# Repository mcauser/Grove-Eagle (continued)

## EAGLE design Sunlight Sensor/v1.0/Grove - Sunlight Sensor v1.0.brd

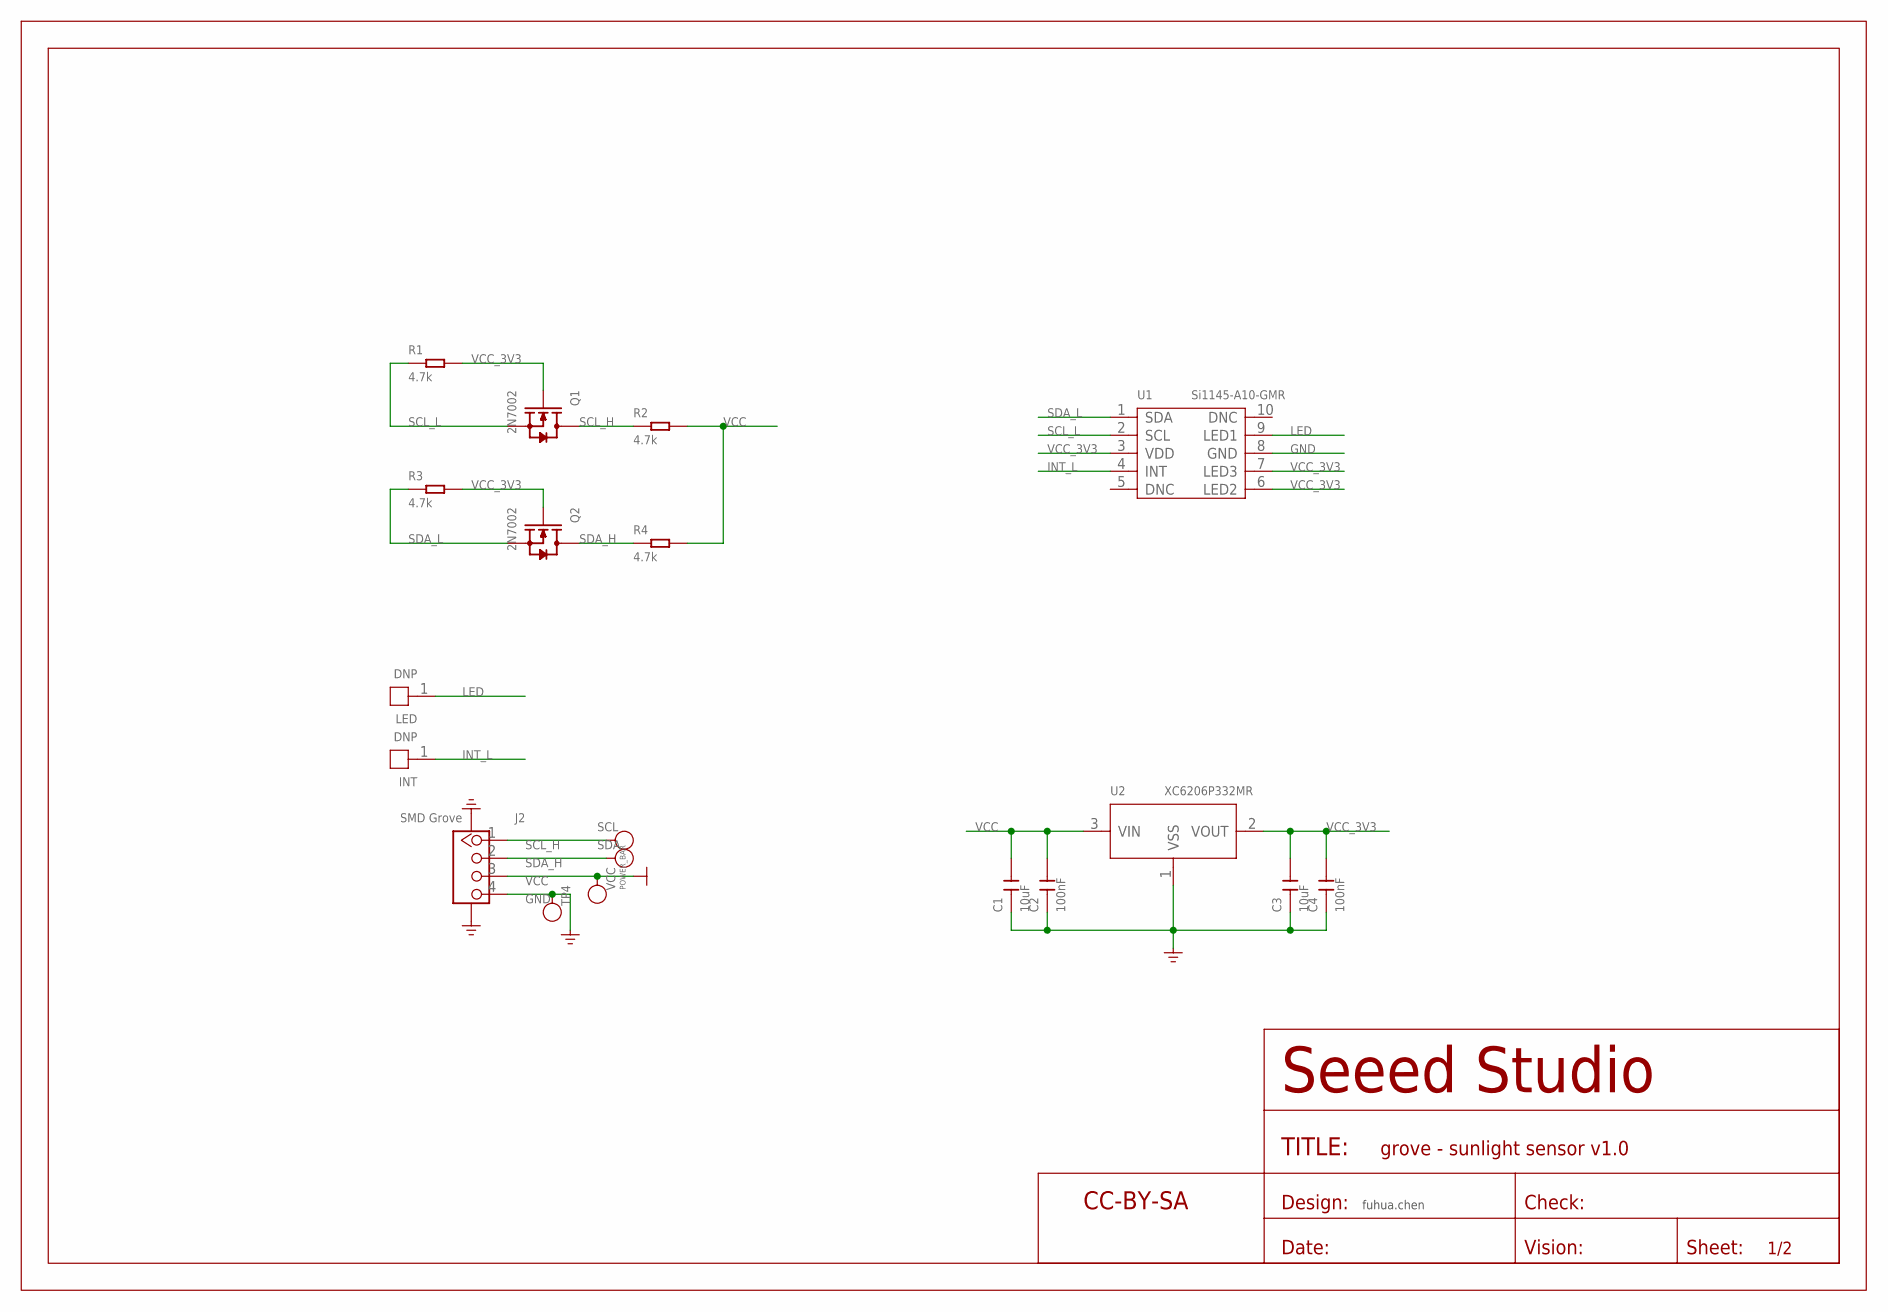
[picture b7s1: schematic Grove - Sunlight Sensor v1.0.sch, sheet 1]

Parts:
C1, C3: 10uF; C0603
C2, C4: 100nF; C0603
FR: SEEEDSTUDIO-OPEN-SCH-FRAME; SEEEDSTUDIO-PCB-FRAME
INT: DNP; 1P-80/40MIL
J2: SMD Grove; HW4-SMD-2.0
LED: DNP; 1P-80/40MIL
Q1, Q2: 2N7002; SOT-23
R1, R2, R3, R4: 4.7k; R0603
SCL: TEST-POINT'4545'; TP-D45MIL
SDA: TEST-POINT'4545'; TP-D45MIL
TP4: TEST-POINT'4545'; TP-D45MIL
U1: Si1145-A10-GMR; DFN10-0.5-2X2MM
U2: XC6206P332MR; SOT-23
VCC: TEST-POINT'4545'; TP-D45MIL

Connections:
GND: C1.1, C2.1, C3.1, C4.1, J2.4, J2.SS1, J2.SS2, TP4.T, U1.8 (GND), U2.1 (VSS)
INT_L: INT.1, U1.4 (INT)
LED: LED.1, U1.9 (LED1)
SCL_H: J2.1, Q1.3 (D), R2.1, SCL.T
SCL_L: Q1.2 (S), R1.1, U1.2 (SCL)
SDA_H: J2.2, Q2.3 (D), R4.1, SDA.T
SDA_L: Q2.2 (S), R3.1, U1.1 (SDA)
VCC: C1.2, C2.2, J2.3, R2.2, R4.2, U2.3 (VIN), VCC.T
VCC_3V3: C3.2, C4.2, Q1.1 (G), Q2.1 (G), R1.2, R3.2, U1.3 (VDD), U1.6 (LED2), U1.7 (LED3), U2.2 (VOUT)

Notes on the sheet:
fuhua.chen

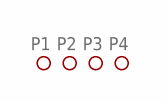
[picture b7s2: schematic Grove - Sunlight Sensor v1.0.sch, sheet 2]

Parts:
P1, P2, P3, P4: PAD-MARK'ANNULAR'; ROUND-MARK-1.0

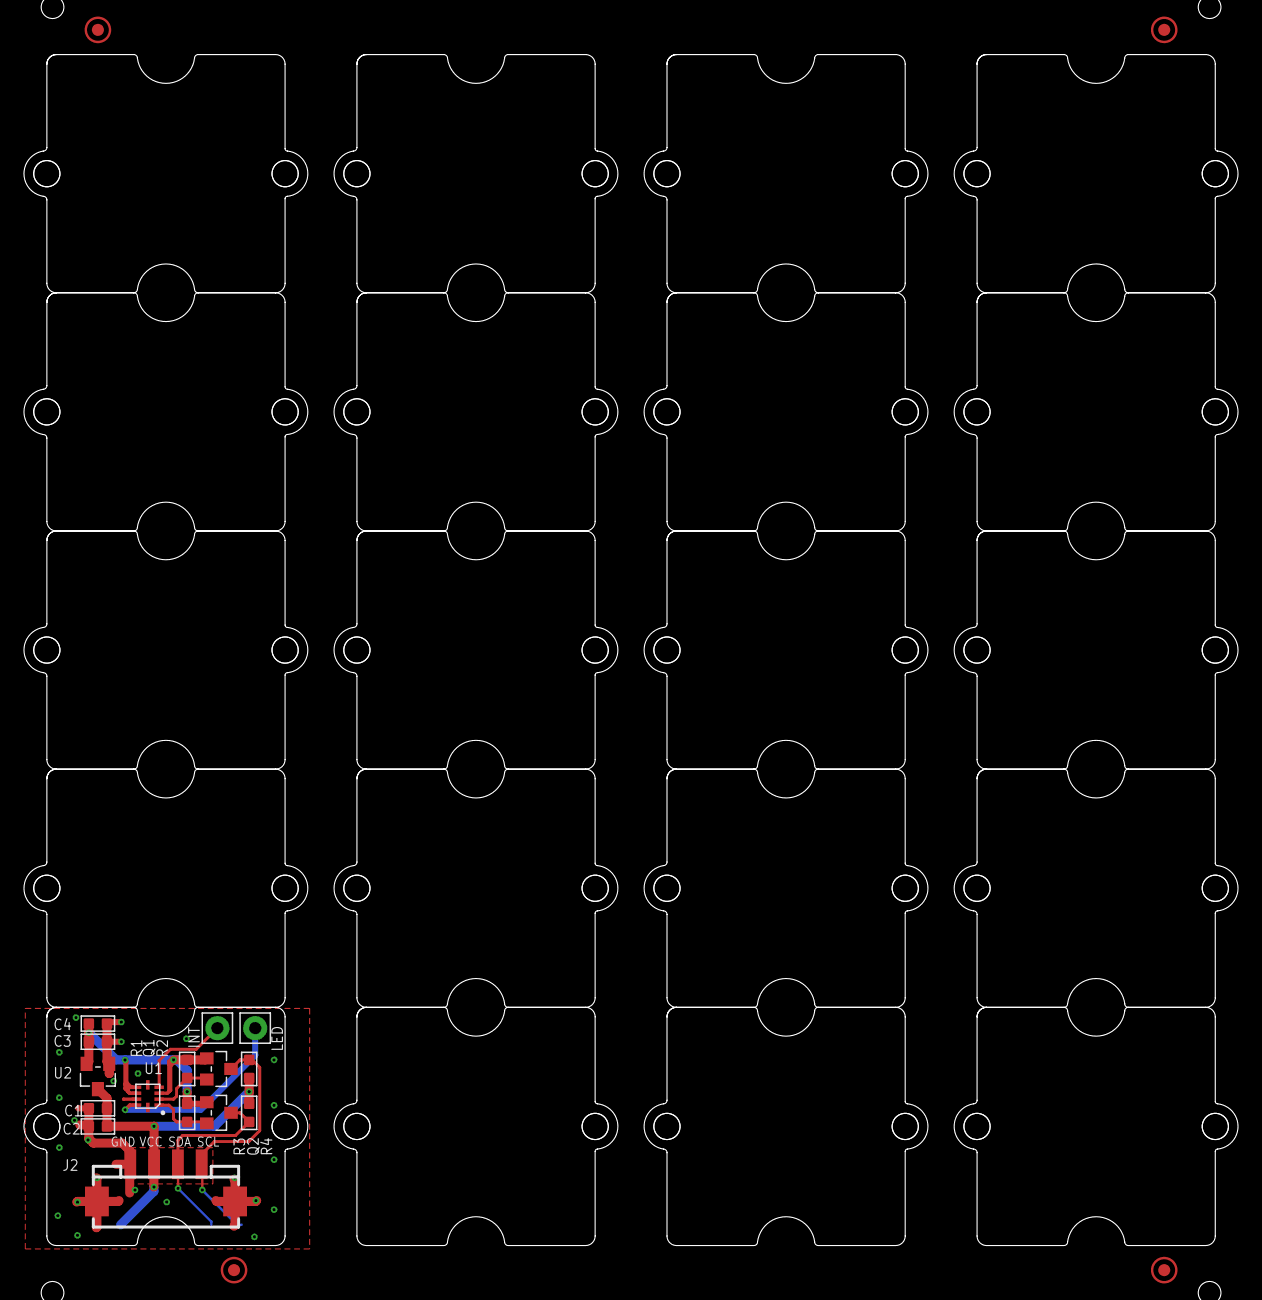
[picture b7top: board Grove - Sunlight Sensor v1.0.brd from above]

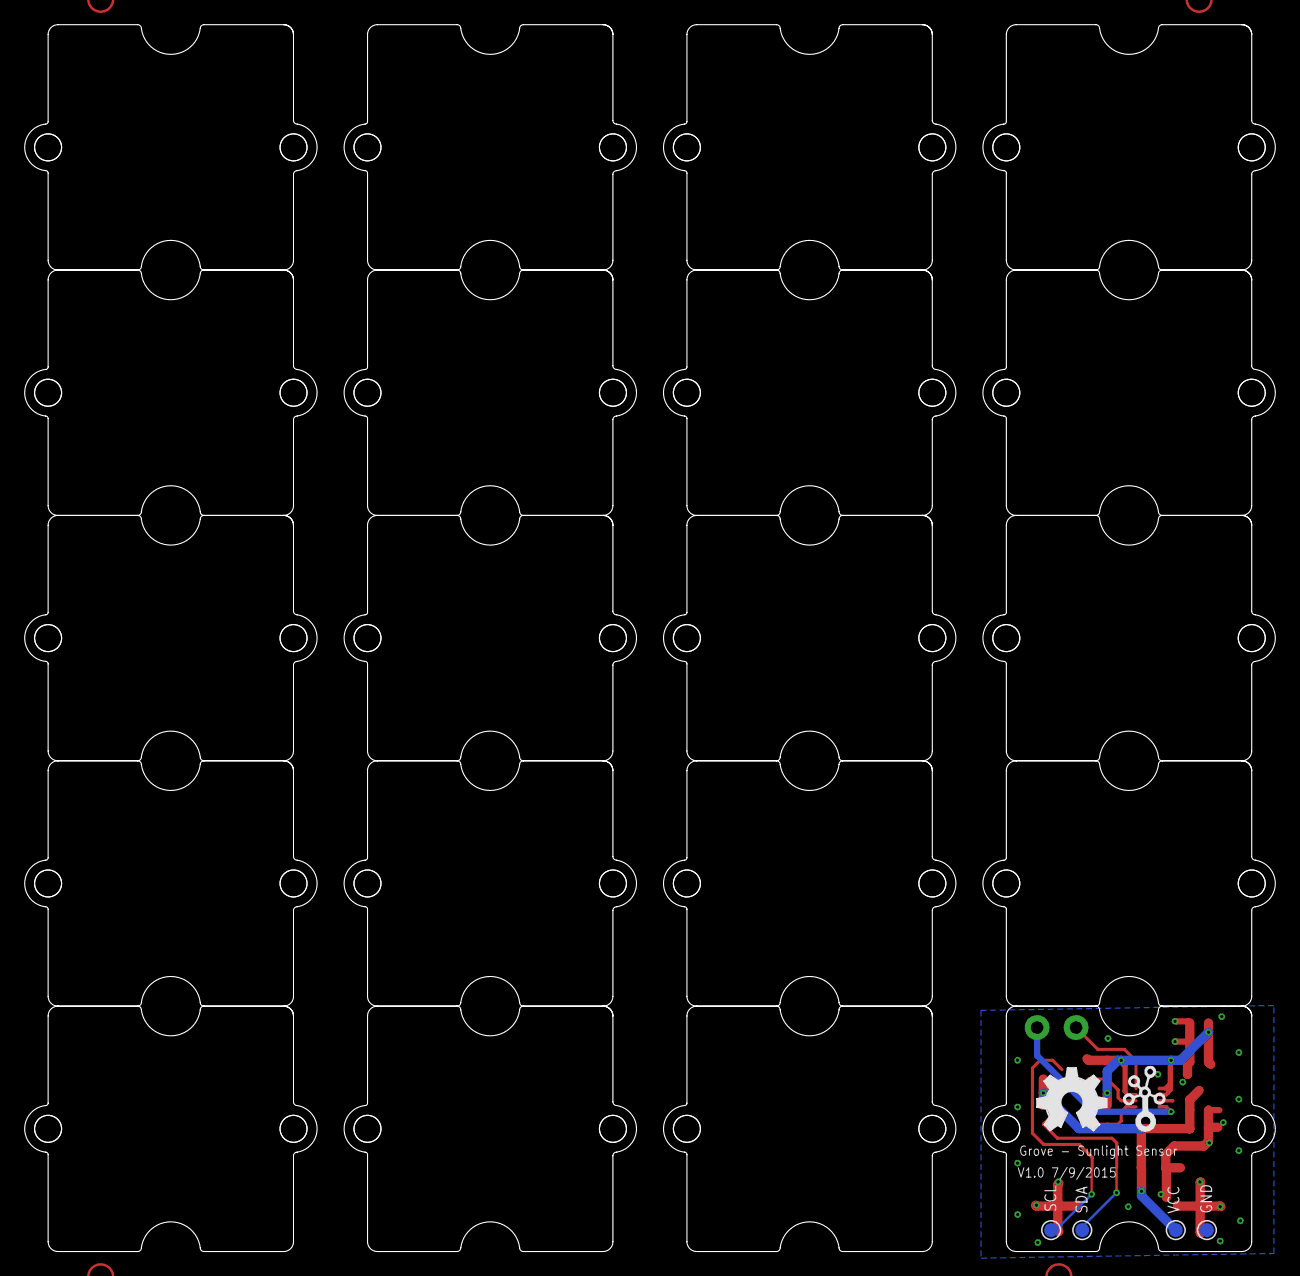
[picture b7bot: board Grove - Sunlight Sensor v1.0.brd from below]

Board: 2 copper layers, 101.9 x 100.0 mm, 46 parts (6 on the bottom side), 9 nets.

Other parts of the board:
U$1: GROVE-SILK-SMALL
U$2, U$4, U$7, U$8, U$9, U$10, U$11, U$12, U$13, U$14, U$15, U$16, U$17, U$18, U$19, U$20, U$21, U$22, U$23, U$24: GROVE-1*1-TEST-PLATFORM
U$3: OSHW_FILLX200_NOTEXT

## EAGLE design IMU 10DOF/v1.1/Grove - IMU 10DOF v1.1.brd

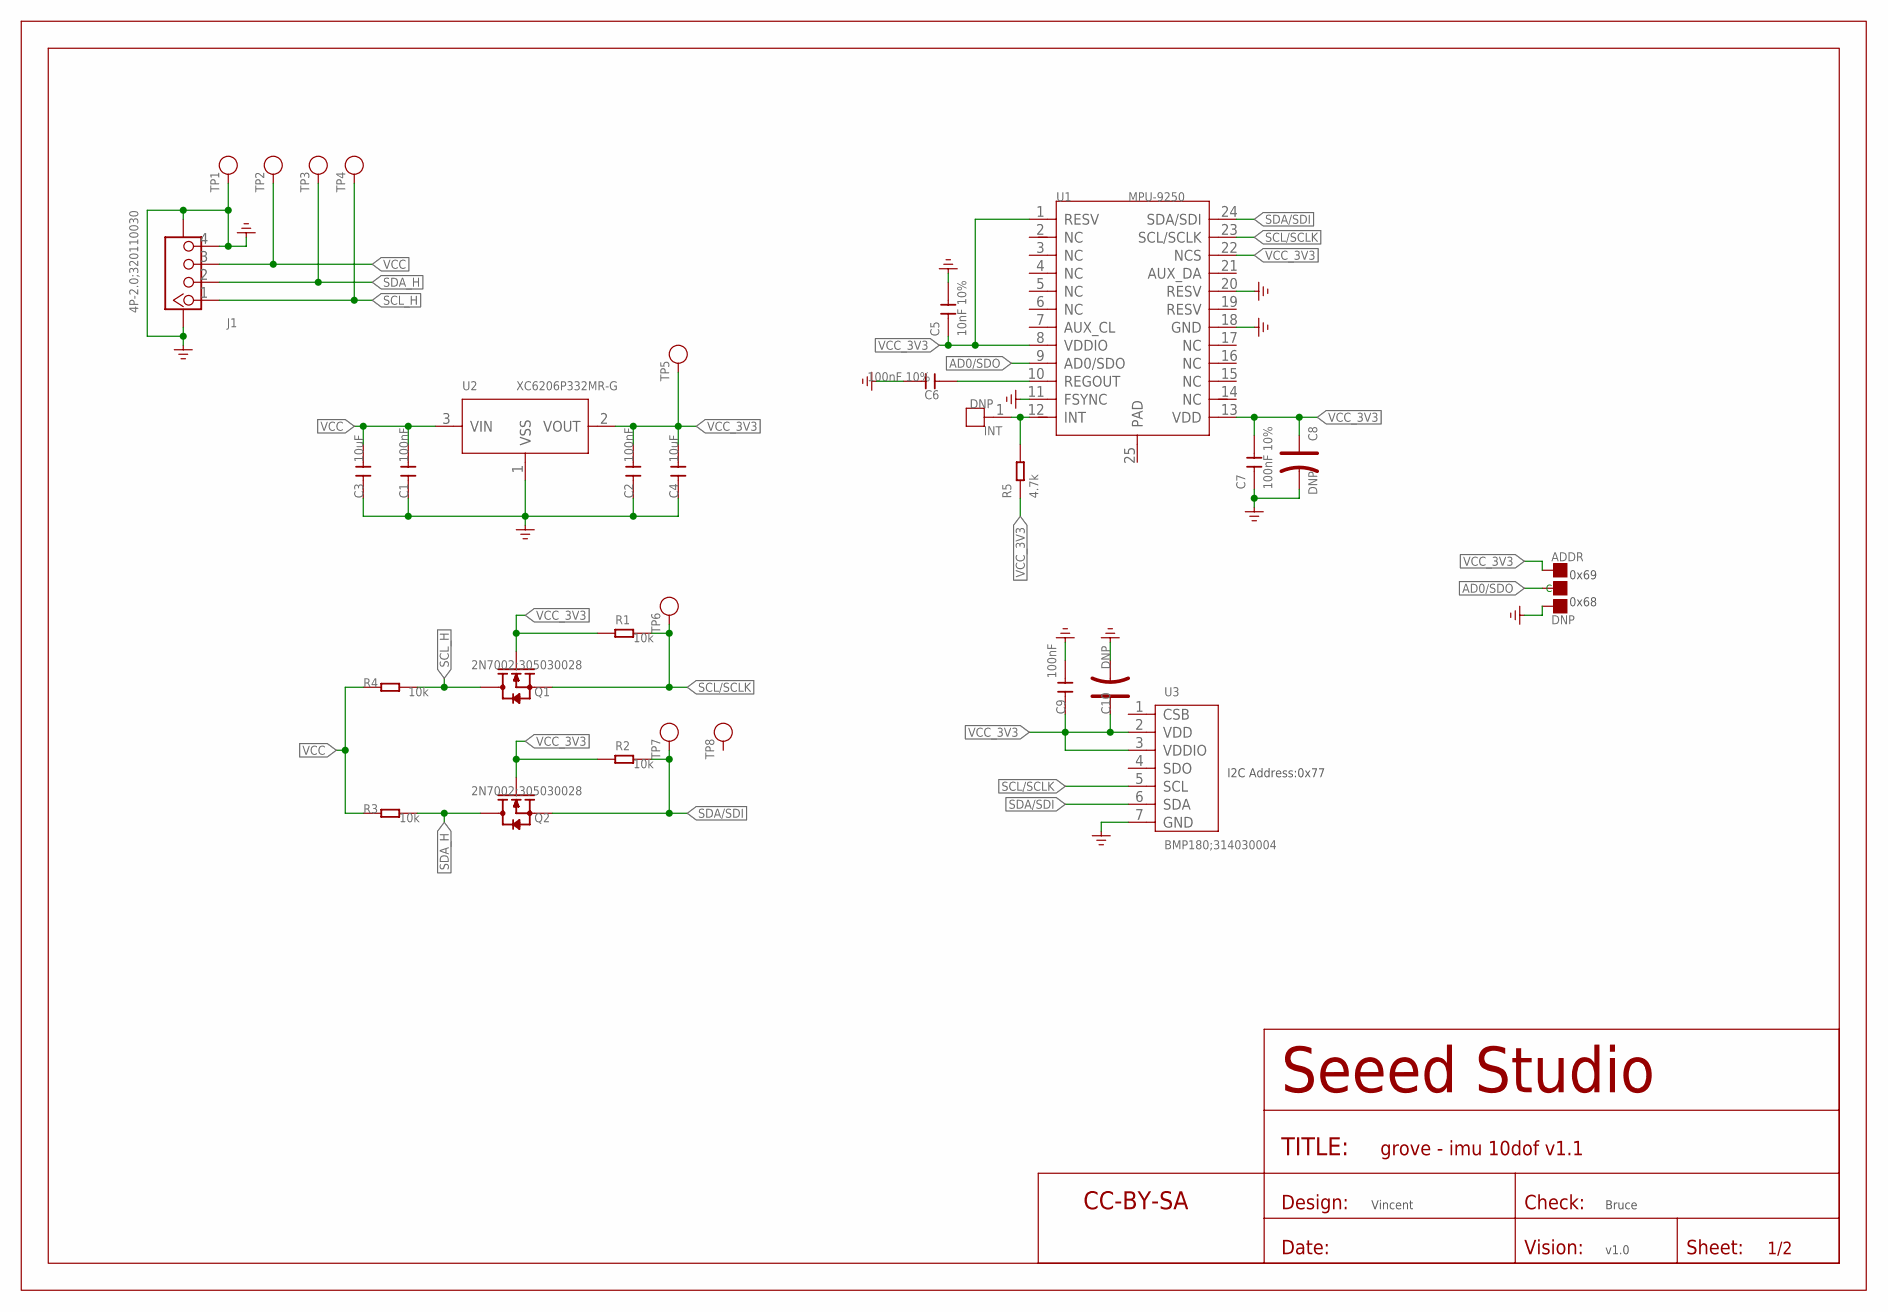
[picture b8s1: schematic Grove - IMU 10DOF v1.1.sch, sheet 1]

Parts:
ADDR: DNP; 3P-SMD-L4.1*W1.5MM
C1, C2, C9: 100nF; C0603
C3, C4: 10uF; C0805
C5: 10nF 10%; C0603
C6, C7: 100nF 10%; C0603
C8, C10: DNP; AVX-A
INT: DNP; 1P-65/35MIL
J1: 4P-2.0;320110030; 4P-SMD-2.0
Q1, Q2: 2N7002;305030028; SOT-23
R1, R2, R3, R4: 10k; R0603
R5: 4.7k; R0603
TP1, TP2, TP3, TP4, TP5, TP6, TP7, TP8: DNP; TP-D45MIL
U1: MPU-9250; LEAD-QFN24
U2: XC6206P332MR-G; SOT-23
U3: BMP180;314030004; LGA-7
U$1: SEEEDSTUDIO-OPEN-SCH-FRAME; SEEEDSTUDIO-PCB-FRAME

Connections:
AD0/SDO: ADDR.MM (C), U1.9 (AD0/SDO)
GND: ADDR.11 (R), C1.1, C2.1, C3.1, C4.1, C5.2, C6.2, C7.1, C8.-, C9.2, C10.-, J1.4, J1.SS1, J1.SS2, TP1.T, U1.11 (FSYNC), U1.18 (GND), U1.20 (RESV), U2.1 (VSS), U3.7 (GND)
unnamed: C6.1, U1.10 (REGOUT)
unnamed: INT.1, R5.2, U1.12 (INT)
SCL/SCLK: Q1.2 (S), R1.2, TP6.T, U1.23 (SCL/SCLK), U3.5 (SCL)
SCL_H: J1.1, Q1.3 (D), R4.2, TP4.T
SDA/SDI: Q2.2 (S), R2.2, TP7.T, U1.24 (SDA/SDI), U3.6 (SDA)
SDA_H: J1.2, Q2.3 (D), R3.2, TP3.T
VCC: C1.2, C3.2, J1.3, R3.1, R4.1, TP2.T, U2.3 (VIN)
VCC_3V3: ADDR.00 (L), C2.2, C4.2, C5.1, C7.2, C8.+, C9.1, C10.+, Q1.1 (G), Q2.1 (G), R1.1, R2.1, R5.1, TP5.T, U1.1 (RESV), U1.8 (VDDIO), U1.13 (VDD), U1.22 (NCS), U2.2 (VOUT), U3.2 (VDD), U3.3 (VDDIO)

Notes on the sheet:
Vincent
Bruce
v1.0
0x69
0x68
I2C Address:0x77

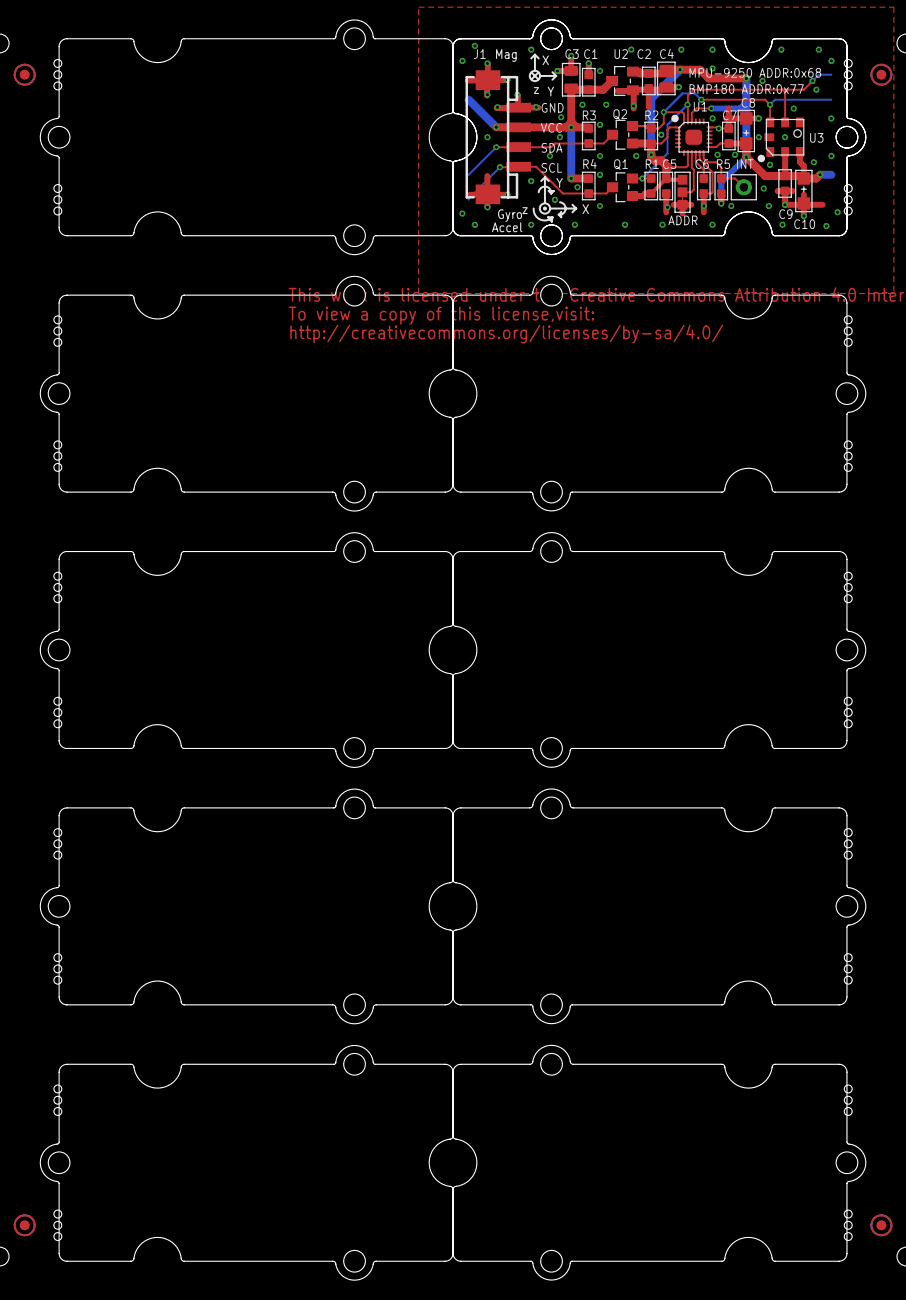
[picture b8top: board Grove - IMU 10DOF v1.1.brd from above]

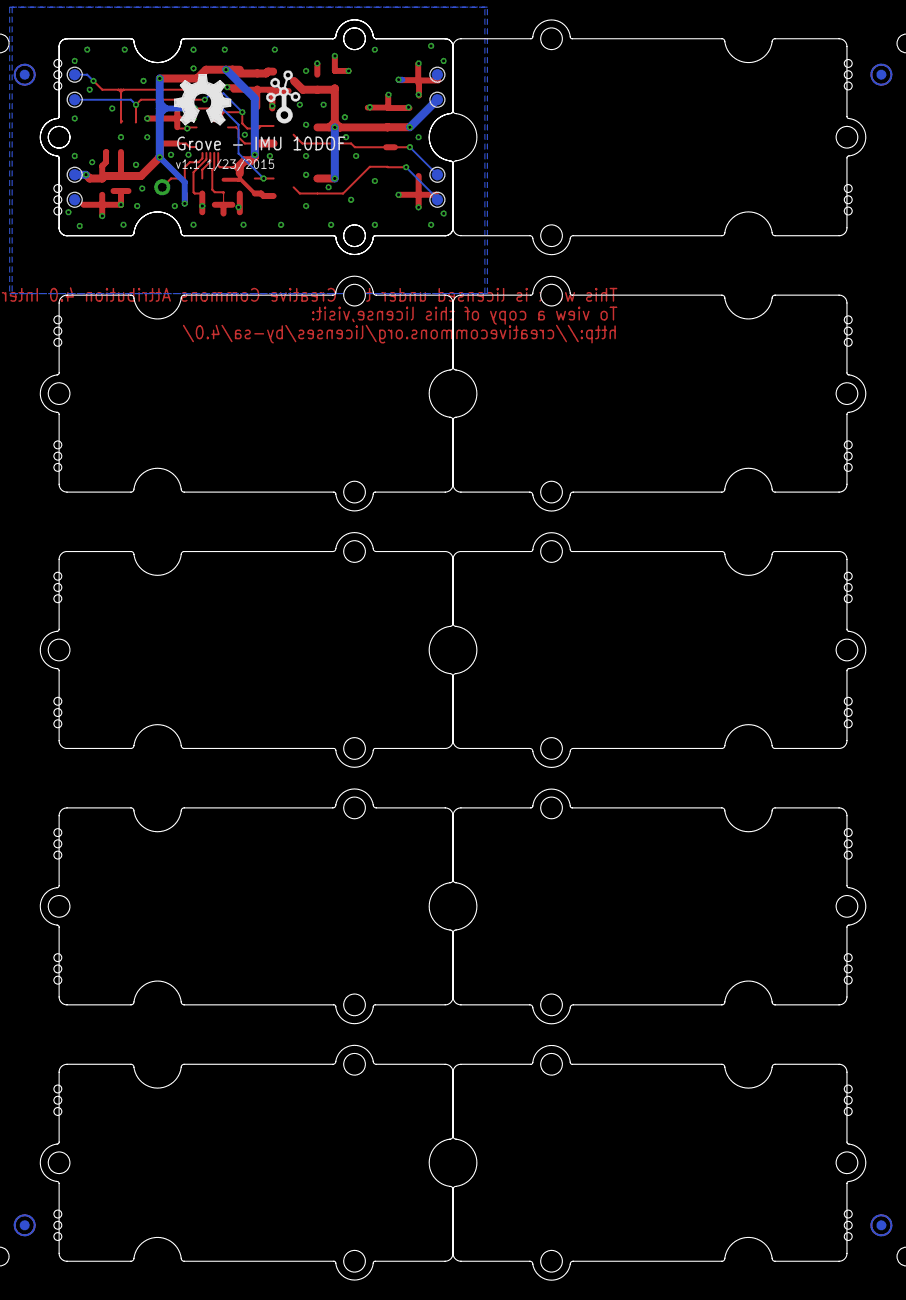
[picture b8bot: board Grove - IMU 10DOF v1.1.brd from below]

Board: 2 copper layers, 83.8 x 128.0 mm, 53 parts (14 on the bottom side), 10 nets.

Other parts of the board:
P1, P2, P3, P4, P5, P6, P7, P8: ROUND-MARK-1.0
U4, U5, U6, U7, U8, U9, U10, U11, U12, U13: GROVE-TEST-PLATFORM
U$15: GROVE-1*2-TEST-PLATFORM
U$16: GROVE-SILK-SMALL
U$17: OSHW_FILLX200_NOTEXT

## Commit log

2015-02-24 Add 2-Coil Latching Relay
2015-02-24 Add 3-Axis Analog Accelerometer
2015-02-24 Add 3-Axis Digital Accelerometer(±1.5g)
2015-02-24 Add 3-Axis Digital Accelerometer(±16g)
2015-02-24 Add 3-Axis Digital Accelerometer(±400g)
2015-02-24 Add 3-Axis Digital Compass
2015-02-24 Add 3-Axis Digital Gyro
2015-02-24 Add 4-Digit Display
2015-02-24 Add 6-Axis Accelerometer & Compass
2015-02-24 Add Air Quality Sensor
2015-02-24 Add Alcohol Sensor
2015-02-24 Add Barometer (High-Accuracy)
2015-02-24 Add Barometer Sensor
2015-02-24 Add Barometer Sensor (BMP180)
2015-02-24 Add Base Shield
2015-02-24 Add Base Shield for IOIO-OTG
2015-02-24 Add Bee Socket
2015-02-24 Add BLE
2015-02-24 Add Button
2015-02-24 Add Buzzer
2015-02-24 Add Chainable RGB LED
2015-02-24 Add Chest Strap Heart Rate Sensor
2015-02-24 Add Circular LED
2015-02-24 Add Collision Sensor
2015-02-24 Add Differential Amplifier
2015-02-24 Add Digital Light Sensor
2015-02-24 Add DMX512
2015-02-24 Add Dry-Reed Relay
2015-02-24 Add Electricity Sensor
2015-02-24 Add Electromagnet
2015-02-24 Add EMG Detector
2015-02-24 Add Encoder
2015-02-24 Add Flame Sensor
2015-02-24 Add FM Receiver
2015-02-24 Add Gas Sensor(MQ2)
2015-02-24 Add Gas Sensor(MQ3)
2015-02-24 Add Gas Sensor(MQ5)
2015-02-24 Add Gas Sensor(MQ9)
2015-02-24 Add Gas Sensor(O2)
2015-02-24 Add Geiger Counter
2015-02-24 Add GPS
2015-02-24 Add GSR Sensor
2015-02-24 Add Hall Sensor
2015-02-24 Add HCHO Sensor
2015-02-24 Add High Temperature Sensor
2015-02-24 Add I2C ADC
2015-02-24 Add I2C Color Sensor
2015-02-24 Add I2C FM Receiver
2015-02-24 Add I2C Hub
2015-02-24 Add I2C Motor Driver
2015-02-24 Add I2C Touch Sensor
2015-02-24 Add IMU 9DOF
2015-02-24 Add Infrared Emitter
2015-02-24 Add Infrared Receiver
2015-02-24 Add Infrared Reflective Sensor
2015-02-24 Add Infrared Temperature Sensor
2015-02-24 Add IR Distance Interrupter
2015-02-24 Add LED
2015-02-24 Add LED Bar
2015-02-24 Add LED Socket Kit
2015-02-24 Add LED String Light
2015-02-24 Add LED Strip Driver
2015-02-24 Add Light Sensor
2015-02-24 Add Line Finder
2015-02-24 Add Loudness Sensor
2015-02-24 Add Luminance Sensor
2015-02-24 Add Magnetic Switch
2015-02-24 Add Mega Shield
2015-02-24 Add Mini Camera
2015-02-24 Add Mini Fan
2015-02-24 Add Moisture Sensor
2015-02-24 Add MOSFET
2015-02-24 Add NFC
2015-02-24 Add NFC Tag
2015-02-24 Add NunChuck
2015-02-24 Add PH Sensor
2015-02-24 Add Piezo Vibration Sensor
2015-02-24 Add PIR Motion Sensor
2015-02-24 Add Protoshield
2015-02-24 Add PS-2 Adapter
2015-02-24 Add Q Touch Sensor
2015-02-24 Add Recorder
2015-02-24 Add Relay
2015-02-24 Add RJ45 Adapter
2015-02-24 Add Rotary Angle Sensor
2015-02-24 Add Rotary Angle Sensor(P)
2015-02-24 Add RTC
2015-02-24 Add Screw Terminal
2015-02-24 Add Serial Bluetooth
2015-02-24 Add Serial LCD
2015-02-24 Add Serial MP3 Player
2015-02-24 Add Single Axis Analog Gyro
2015-02-24 Add Slide Potentiometer
2015-02-24 Add Solid State Relay
2015-02-24 Add Sound Recorder
2015-02-24 Add Sound Sensor
2015-02-24 Add SPDT Relay(30A)
2015-02-24 Add Speaker
2015-02-24 Add Switch(P)
2015-02-24 Add Temperature & Humidity Sensor
2015-02-24 Add Temperature & Humidity Sensor Pro
2015-02-24 Add Temperature & Humidity Sensor (High-Accuracy & Mini)
2015-02-24 Add Temperature Sensor
2015-02-24 Add Thumb Joystick
2015-02-24 Add Tilt Switch
2015-02-24 Add Touch Sensor
2015-02-24 Add UV Sensor
2015-02-24 Add Variable Color LED
2015-02-24 Add Vibration Motor
2015-02-24 Add Voltage Divider
2015-02-24 Add Water Sensor
2015-02-24 Add XBee Carrier
2015-02-25 Add readme
2015-03-02 Add Tilt Switch v1.1
2015-03-02 Add IMU 10DOF v1.0
2015-03-02 Add EL Driver v1.0
2015-03-02 Add Grove-BLE (dual model) v1.0
2015-03-02 Add Air Quality Sensor v1.3
2015-03-02 Add 3-Axis Digital Accelerometer(±16g) v1.3
2015-03-02 Add 6-Axis Accelerometer & Compass v2.0
2015-03-17 Add IMU 9DOF v2.0
2015-03-17 Add Mega Shield v1.1
2015-03-24 Add Alcohol Sensor v1.2
2015-03-24 Add Finger-clip Heart Rate Sensor v1.0
2015-04-08 Add Gesture v1.0
2015-04-08 Add OLED Display 96x96 v2.1
2015-04-14 Add Multichannel Gas Sensor v1.0
2015-04-14 Add Node v1.0
2015-04-14 Add Digital Infrared Temperature Sensor v1.0
2015-04-24 Add Temperature & Humidity Sensor (HDC1000) v1.0
2015-05-14 Add Piezo Vibration Sensor v1.1
2015-05-14 Add Techbox Tricks v1.0
2015-06-09 Add Gas Sensor(MQ2) v1.4
2015-06-09 Add Gas Sensor(MQ3) v1.4
2015-06-09 Add Gas Sensor(MQ5) v1.4
2015-06-09 Add Gas Sensor(MQ9) v1.4
2015-08-24 Add Base Shield for NodeMCU v1.0
2015-08-24 Add NFC v1.0
2015-08-24 Add Mini I2C Motor Driver v1.0
2015-08-24 Add Joint v2.0
2015-10-21 Add IMU 10DOF v1.1
2015-10-21 Add Sunlight Sensor v1.0
2015-10-21 Add Haptic Motor v0.9
2015-10-21 Add Recorder v2.0
2015-10-21 Add Water Atomization v1.0
2015-10-21 Add LED Socket Kit v1.3
2015-10-21 Add Mini Track ball v1.0
2015-10-21 Update Buy links and SKUs
2015-12-10 Add Mouse Encoder v1.0
